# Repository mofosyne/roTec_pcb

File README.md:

# roTec_pcb

<details>
<summary>Revision 5.4 (Though Hole Version)</summary>

| Front (Through Hole Version)        | Back (Through Hole Version)       |
|:------------------------------------|:----------------------------------|
|  |  |

[Release Files For PCB Revision 5.4 (Though Hole Version)](https://github.com/mofosyne/roTec_pcb/releases/tag/rev5.4)

</details>

<details>
<summary>Revision 5.3 (Surface Mount)</summary>

| Front                               | Back                              |
|:------------------------------------|:----------------------------------|
|  |  |

[Release Files For PCB Revision 5.3 (All features except for GPS tested) (Recommended)](https://github.com/mofosyne/roTec_pcb/releases/tag/rev5.3)

</details>

RoTec is a low-cost nRF52 device with the form-factor of the Heltec v2, v3, & v4 devices compatible with [Meshtastic](https://meshtastic.org/)®, designed for use with rotary encoders as well as being easy to follow for less technical users.

The history of this design is that it is a fork of [Jacob's](https://github.com/jtljac) fork of the fakeTec.

This design is specifically based off of [Šimon Hořánek's](https://github.com/ShimonHoranek) [fakeTec V5 Rev. B](https://github.com/gargomoma/fakeTec_pcb/issues/24), licensed under [CERN-OHL-P-2.0](https://choosealicense.com/licenses/cern-ohl-p-2.0/).

**[For more meshtastic/meshcore/lora DIY nodes, do check this list out!](https://github.com/porkcube/meshtastic-diy-nodes)**

## Design Documentations (Through Hole Version)

* [Schematic as pdf](./Circuit_Through_Hole/documentation/roTec_schematic.pdf)
* [Schematic Bill Of Materials](./Circuit_Through_Hole/documentation/roTec_bom.csv)

* You may also want to manufacture [EC11 Rotary Encoder Horizontal Breakout Board](https://github.com/mofosyne/kicad_useful_pcbs/tree/main?tab=readme-ov-file#ec11-horizontal-breakout-board), so you can more easily wire the rotary encoder to the roTec via a JST-SH-4 cable.

This has the same parts list as the SMD version, but with a few parts subtracted.

## Design Documentations (Surface Mount Version)

* [Schematic as pdf](./Circuit/documentation/roTec_schematic.pdf)
* [Schematic Bill Of Materials](./Circuit/documentation/roTec_bom.csv)

* You may also want to manufacture [EC11 Rotary Encoder Horizontal Breakout Board](https://github.com/mofosyne/kicad_useful_pcbs/tree/main?tab=readme-ov-file#ec11-horizontal-breakout-board), so you can more easily wire the rotary encoder to the roTec via a JST-SH-4 cable.

### Bill of materials

<details>
<summary>Bill of material. For full details and descriptions refer to the csv BOM above instead.</summary>

| Reference           | Value                      | Qty | Manufacturer                     | MPN                  | Package                                | Datasheet                                                                                                                                     | Manufacturer Parts Link (MPL)                                                                                                                                                              | Shopping                                                                                                                                         |
|---------------------|----------------------------|-----|----------------------------------|----------------------|----------------------------------------|-----------------------------------------------------------------------------------------------------------------------------------------------|--------------------------------------------------------------------------------------------------------------------------------------------------------------------------------------------|--------------------------------------------------------------------------------------------------------------------------------------------------|
| J9                  | Molex PicoBlade 0532610271 | 1   | CJT(Changjiang Connectors)       | A1251WR-S-2P         | SMD,P=1.25mm,Surface Mount,Right Angle | [datasheet](https://www.molex.com/content/dam/molex/molex-dot-com/products/automated/en-us/salesdrawingpdf/532/53261/532610271_sd.pdf?inline) | [lcsc](https://www.lcsc.com/product-detail/C225111.html)                                                                                                                                   | [LCSC](https://www.lcsc.com/search?q=0532610271&s_z=n_0532610271)                                                                                |
| U1                  | XB8089D0 BMS               | 1   | XySemi                           | XB8089D0             | SOIC-8                                 | [datasheet](https://www.lcsc.com/datasheet/lcsc_datasheet_2410121637_XySemi-XB8089D0_C2760005.pdf                                           ) | [lcsc](https://www.lcsc.com/product-detail/C2760005.html?s_z=n_XySemi%2520XB8089D0)                                                                                                        | [LCSC](https://www.lcsc.com/search?q=XB8089D0&s_z=n_XB8089D0)                                                                                    |
| Q1,Q2,Q3            | n-chn mosfet               | 3   | Alpha & Omega Semiconductor Inc. | AO3400A              | SOT-23-3L                              | [datasheet](http://www.aosmd.com/pdfs/datasheet/AO3400A.pdf                                                                                 ) | [lcsc](https://www.lcsc.com/product-detail/C20917.html?s_z=n_AO3400A)                                                                                                                      | [LCSC](https://www.lcsc.com/search?q=MOSFET%2520N-CH%2520SOT-23-3L&s_z=n_MOSFET%2520N-CH%2520SOT-23-3L)                                          |
| BZ1                 | Buzzer 5020                | 1   | HYDZ                             | HYG-5020A            | SMD,5x5mm                              | [datasheet](https://www.lcsc.com/datasheet/C7544810.pdf                                                                                     ) | [lcsc](https://www.lcsc.com/product-detail/C7544810.html?s_z=n_buzzer%25205020)                                                                                                            | [LCSC](https://www.lcsc.com/search?q=Buzzer_5020&s_z=n_Buzzer_5020)                                                                              |
| J38,J50             | JST-SH-4                   | 2   | JST Sales America Inc.           | SM04B-SRSS-TB        | SMD,P=1mm,Surface Mount,Right Angle    | [datasheet](https://www.jst-mfg.com/product/pdf/eng/eSH.pdf                                                                                 ) | [lcsc](https://www.lcsc.com/product-detail/C51940130.html?s_z=n_SM04B-SRSS-TB)                                                                                                             | [LCSC](https://www.lcsc.com/search?q=SM04B-SRSS-TB&s_z=n_SM04B-SRSS-TB)                                                                          |
| OLED1               | I2C OLED Module            | 1   |                                  |                      | Through Hole                           | [datasheet](https://cdn-shop.adafruit.com/datasheets/SSD1306.pdf                                                                            ) | [aliexpress](https://www.aliexpress.com/item/1005008738379315.html)                                                                                                                        | [aliexpress](https://www.aliexpress.com/w/wholesale-0.96-Inch-OLED-Display-Module.html)                                                          |
| U3                  | nice!nano v2               | 1   | Nice!                            | nice!nano v2         | nice!nano v2                           | [datasheet](https://nicekeyboards.com/docs/nice-nano/pinout-schematic                                                                       ) | [aliexpress](https://www.aliexpress.com/item/1005010222966695.html)                                                                                                                        | [aliexpress](https://www.aliexpress.com/w/wholesale-NRF52840-1%2525252d10PCS.html)                                                               |
| SW1                 | Reset                      | 1   | XUNPU                            | TS-1088R-02026       | SMD,4x3mm                              | [datasheet](https://www.lcsc.com/datasheet/C455280.pdf                                                                                      ) | [lcsc](https://www.lcsc.com/product-detail/C455280.html?s_z=n_TS-1088R-02026)                                                                                                              | [LCSC](https://www.lcsc.com/search?q=TS-1088R-02026&s_z=n_TS-1088R-02026)                                                                        |
| SW2                 | SW_Push                    | 1   | XUNPU                            | TS-1088R-02026       | SMD,4x3mm                              | [datasheet](https://www.lcsc.com/datasheet/C455280.pdf                                                                                      ) | [lcsc](https://www.lcsc.com/product-detail/C455280.html?s_z=n_TS-1088R-02026)                                                                                                              | [LCSC](https://www.lcsc.com/search?q=TS-1088R-02026&s_z=n_TS-1088R-02026)                                                                        |
| R1,R2,R3,R9,R10,R11 | 10k                        | 6   |                                  |                      | 0805                                   |                                                                                                                                               |                                                                                                                                                                                            | [LCSC](https://www.lcsc.com/search?q=10K%25200805&s_z=n_10K%25200805)                                                                            |
| R4                  | 680K                       | 1   |                                  |                      | 0805                                   |                                                                                                                                               |                                                                                                                                                                                            | [LCSC](https://www.lcsc.com/search?q=680K%25200805&s_z=n_680K%25200805)                                                                          |
| R5                  | 1.0M                       | 1   |                                  |                      | 0805                                   |                                                                                                                                               |                                                                                                                                                                                            | [LCSC](https://www.lcsc.com/search?q=1M%25200805&s_z=n_1M%25200805)                                                                              |
| R6                  | 1k                         | 1   |                                  |                      | 0805                                   |                                                                                                                                               |                                                                                                                                                                                            | [LCSC](https://www.lcsc.com/search?q=1k%25200805&s_z=n_1k%25200805)                                                                              |
| SW3                 | RotaryEncoder_Switch       | 1   | Same Sky (Formerly CUI Devices)  | ACZ11BR1E-15KQA1-12C | EC11                                   | [datasheet](https://www.cuidevices.com/product/resource/acz11.pdf                                                                           ) | [aliexpress](https://www.aliexpress.com/item/1005010398201852.html) or [digikey](https://www.digikey.com.au/en/products/detail/same-sky-formerly-cui-devices/ACZ11BR1E-15KQA1-12C/1923334) | [aliexpress](https://www.aliexpress.com/w/wholesale-rotary-encoder-EC11-horizontal.html) or [digikey](https://www.digikey.com.au/short/7v5m7j9j) |
| U2                  | HT-RA62                    | 1   | Heltec                           | HT-RA62              | HT-RA62                                | [datasheet](https://resource.heltec.cn/download/HT-RA62/HT-RA62(Rev1.1).pdf                                                                 ) | [aliexpress](https://www.aliexpress.com/item/1005005543917617.html)                                                                                                                        | [aliexpress](https://www.aliexpress.com/w/wholesale-HT%2525252dRA62.html)                                                                        |
| C1,C2               | 100nF                      | 2   |                                  |                      | 0805                                   |                                                                                                                                               |                                                                                                                                                                                            | [LCSC](https://www.lcsc.com/search?q=100nF%25200805&s_z=n_100nF%25200805)                                                                        |
| M1                  | ERM Motor                  | 1   | Seeed Technology Co., Ltd        | 316040001            | Wire Leads                             | [datasheet](https://mm.digikey.com/Volume0/opasdata/d220001/medias/docus/2234/1020-15-003-001_Spec.pdf                                      ) | [digikey](https://www.digikey.com.au/en/products/detail/seeed-technology-co-ltd/316040001/5487672)                                                                                         | [aliexpress](https://www.digikey.com.au/short/332zpfdb)                                                                                          |

Purchase Tips:
* You can often buy SMD resistor kits in booklets from most places like amazon or aliexpress.
* Both nice!nano and promicro versions are supported
* You can swap the AO3400A n-channel mosfet with other higher current mosfet like SI2312 as long as the pins and packaqe size matches.
* Vibrations motors can be purchased in bulk pretty cheaply in aliexpress, ebay, amazon, etc...
* XB8089D0 BMS can be skipped if your battery have integrated battery protection already
* JST-SH-4 is optional if you want to solder the rotary encoder, gps, or i2c sensors directly onto the solder pads provided on the board instead
* For GPS support you can buy either ATGM336H or GY-GPS6MV2 modules
* Any OLED screen can be used. Pick one that is designed for your case. Often it's an SSD1306 controller based OLED screen.
* Any lora radios seen inside this [reference schematic](https://github.com/meshtastic/firmware/blob/develop/variants/nrf52840/diy/nrf52_promicro_diy_tcxo/Schematic_Pro-micro_Pinouts_2025-12-04.pdf) that fits the footprint and pinout is supported
  - Just like the faketecs you can also use RA-01SH.
* This design supports 3 different battery connectors types
  - Molex Picoblade 2-Pin
    - MPC: Molex, MPN: 0532610271
    - MPC: CJT (Changjiang Connectors), MPN: A1251WR-S-2P
    - Pitch: 1.25mm
    - Used By: HelTec LoRa 32
  - JST PH 2-Pin
    - MPN: S2B-PH-SM4-TB
    - Pitch: 2.00mm 
    - Used By: RAK19007 WisBlock
  - Direct wiring. 
    - e.g. JST-PH-2 but as an external wire like this [aliexpress product](https://www.aliexpress.com/item/1005002564191148.html)

</details>

## Setting Up Device

### Configure

Included in this repository is `roTec_module_config.yaml` which when you run below command will configure the buzzer, vibration motor and encoder.

```
PORT=/dev/ttyACM0 # Set to the serial port of the roTec after flashing
meshtastic --port $PORT --info
meshtastic --port $PORT --configure roTec_module_config.yaml
meshtastic --port $PORT --reboot
```

Alternatively you could manually use the web interface to set the settings using <client.meshtastic.org> as shown below
(No GPS settings it's already enabled by default if the module is installed).

#### Rotary Encoder Settings:

| Settings                                          | Value   |
|---------------------------------------------------|---------|
| module_config.cannedMessage.allowInputSource      | rotEnc1 |
| module_config.cannedMessage.enabled               | true    |
| module_config.cannedMessage.inputbrokerEventCcw   | RIGHT   |
| module_config.cannedMessage.inputbrokerEventCw    | LEFT    |
| module_config.cannedMessage.inputbrokerEventPress | SELECT  |
| module_config.cannedMessage.inputbrokerPinA       | 33      |
| module_config.cannedMessage.inputbrokerPinB       | 34      |
| module_config.cannedMessage.inputbrokerPinPress   | 39      |
| module_config.cannedMessage.rotary1Enabled        | true    |

#### Vibration Notification Settings:

| Settings                                             | Value |
|------------------------------------------------------|-------|
| module_config.externalNotification.enabled           | true  |
| module_config.externalNotification.alertBell         | true  |
| module_config.externalNotification.alertBellVibra    | true  |
| module_config.externalNotification.alertMessageVibra | true  |
| module_config.externalNotification.outputVibra       | 8     |

#### Buzzer Settings:

**Note you have to override buzzer gpio in config device page**

| Settings                                              | Value                                                                                                     |
|-------------------------------------------------------|-----------------------------------------------------------------------------------------------------------|
| config.device.buzzerGpio                              | 6                                                                                                         |
| module_config.externalNotification.enabled            | true                                                                                                      |
| module_config.externalNotification.alertBell          | true                                                                                                      |
| module_config.externalNotification.alertBellBuzzer    | true                                                                                                      |
| module_config.externalNotification.alertMessageBuzzer | true                                                                                                      |
| module_config.externalNotification.outputBuzzer       | 6                                                                                                         |
| module_config.externalNotification.usePwm             | true                                                                                                      |
| ringtone                                              | `24:d=32,o=5,b=565:f6,p,f6,4p,p,f6,p,f6,2p,p,b6,p,b6,p,b6,p,b6,p,b,p,b,p,b,p,b,p,b,p,b,p,b,p,b,1p.,2p.,p` |

## Features
- Small size based on Heltec v3: You can use the same cases!
- Lora with Heltec's HT-RA62
- Uses a [n!cenano](https://nicekeyboards.com/nice-nano/) or 
  [NRF52840 ProMicro](https://github.com/joric/nrfmicro/wiki/Alternatives#supermini-nrf52840l)
- BMS For low voltage cutout to prevent LiPo Overdraining
- Battery level sensing
- JST PH2.0mm connector for batteries
- I2C side ports ready to connect an OLED SSD1306 screen.
- Pads for connecting an encoder for canned messages
- Pads for connecting a serial GPS module
- MOSFETs for switching high current components
  - Using a solder pad jumper, MOSFET 1 can chose between the GPS module ground to enable power saving the GPS module, 
    or a regular pad like MOSFETs 2 & 3.
- 2mm mounting holes

## Modifications from fakeTec V5 Rev. B
- Cleaned up schematic
  - Changed Pins representing sides of MCUs to symbols fully representing said MCU
  - Changed labels to my preferred naming scheme
  - Updated/Cleaned up symbol fields to make each component easier to find
    - MPN: Manufacturer Parts Number
    - MPD: Manufacturer Parts Description
    - MPL: Manufacturer Parts Link
    - Shopping: Link to search pages used to locate parts. Useful for finding alternatives.
- Setup netclasses
- Shifted pads `P1.01`, `P1.02`, and `P1.07` to where I'm pretty sure they're supposed to be
- Removed jumper for BMS
  - I will always install a BMS
- Removed jumper for GPS/FET1 Drain to FET1
  - Only one will be connected at a time, probably no difference if this is permanently connected to both
- Switched mosfets to AO3400A
  - I already have these and they're a drop in replacement
- Changed all resistors and Capacitors to 805 sized
  - I already have all the resistors in this size
- Added pullup resistors to rotary encoder pads
  - These probably support internal pullups, but just to be safe
- Added ground pad to rotary encoder pads
- Changed battery connector to a JST PH-2.0mm
  - Struggled to find JST 1.25 connectors
  - PH-2.0mm are also apparently more reliable
- Removed lots of silkscreen text
  - Don't need values or component names, just component references
  - Most of it was overlapping
- Moved BMS to side
  - Keeps it out the way of the battery connector
- Added a lot more stitching between front and back ground planes
- Removed vias from on top of silkscreen and off of pads
- Attempted to reduce layer crossings
- Added test pads for the nice!nano/promicro to help users to figure out if the pads is correctly soldered down.
- Added connectors recommended by [this hackaday article ](https://hackaday.com/2022/05/04/the-connector-zoo-i2c-ecosystems) for easy attachment for i2c devices. Pads also exposed in case you want to solder the i2c device down.
- Added buzzer pads so that buzzer can be included in a more compact manner.
- Added pads to expose all the GPIO pins in case users want to use the GPIO for other purpose.
- Added additional marking to indicate resistance and capacitor values
- Added BMS bypass in case users are using batteries with integrated protection already

# Variants

(aka firmware files)

| Version      | Lora Modules                     | Official Repo link                                                                                                                                          | Unofficial Repo link                                                                                                                                                                |
|:-------------|:---------------------------------|:------------------------------------------------------------------------------------------------------------------------------------------------------------|:------------------------------------------------------------------------------------------------------------------------------------------------------------------------------------|
| With TCXO    | EByte E22/E220-xxxM-22S/HT-RA62  | <a href="https://github.com/meshtastic/firmware/tree/master/variants/nrf52840/diy/nrf52_promicro_diy_tcxo" target="_blank">Official repo - With TCXO</a>    | <a href="https://github.com/mrekin/MeshtasticCustomBoards/tree/main/firmware/variants/nrf52840/diy/promicro_diy_m" target="_blank">With TCXO</a> @mrekin/MeshtasticCustomBoards     |
| Without TCXO | EByte E22/E220-xxxMM-22S/RA-01SH | <a href="https://github.com/meshtastic/firmware/tree/master/variants/nrf52840/diy/nrf52_promicro_diy_xtal" target="_blank">Official repo - Without TCXO</a> | <a href="https://github.com/mrekin/MeshtasticCustomBoards/tree/main/firmware/variants/nrf52840/diy/promicro_diy_mm" target="_blank">Without TCXO</a> @mrekin/MeshtasticCustomBoards |

> If you don't want to build your own image use <a href="https://flasher.meshtastic.org/" target="_blank">the official web flasher</a>. Select the `NRF52 Pro-micro DIY` under `Community Supported Devices` as your target device.

# Supported Cases

Refer to [this page](./Cases/README.md) for details on supported cases that this design will fit into.

# About Meshtastic
[Meshtastic](https://meshtastic.org/)® is a registered trademark of Meshtastic LLC. Meshtastic software components are released under various licenses, see github for details.

# Disclaimer
No warranty is provided.
You use it at your own risk and take the responsibility upon yourself.

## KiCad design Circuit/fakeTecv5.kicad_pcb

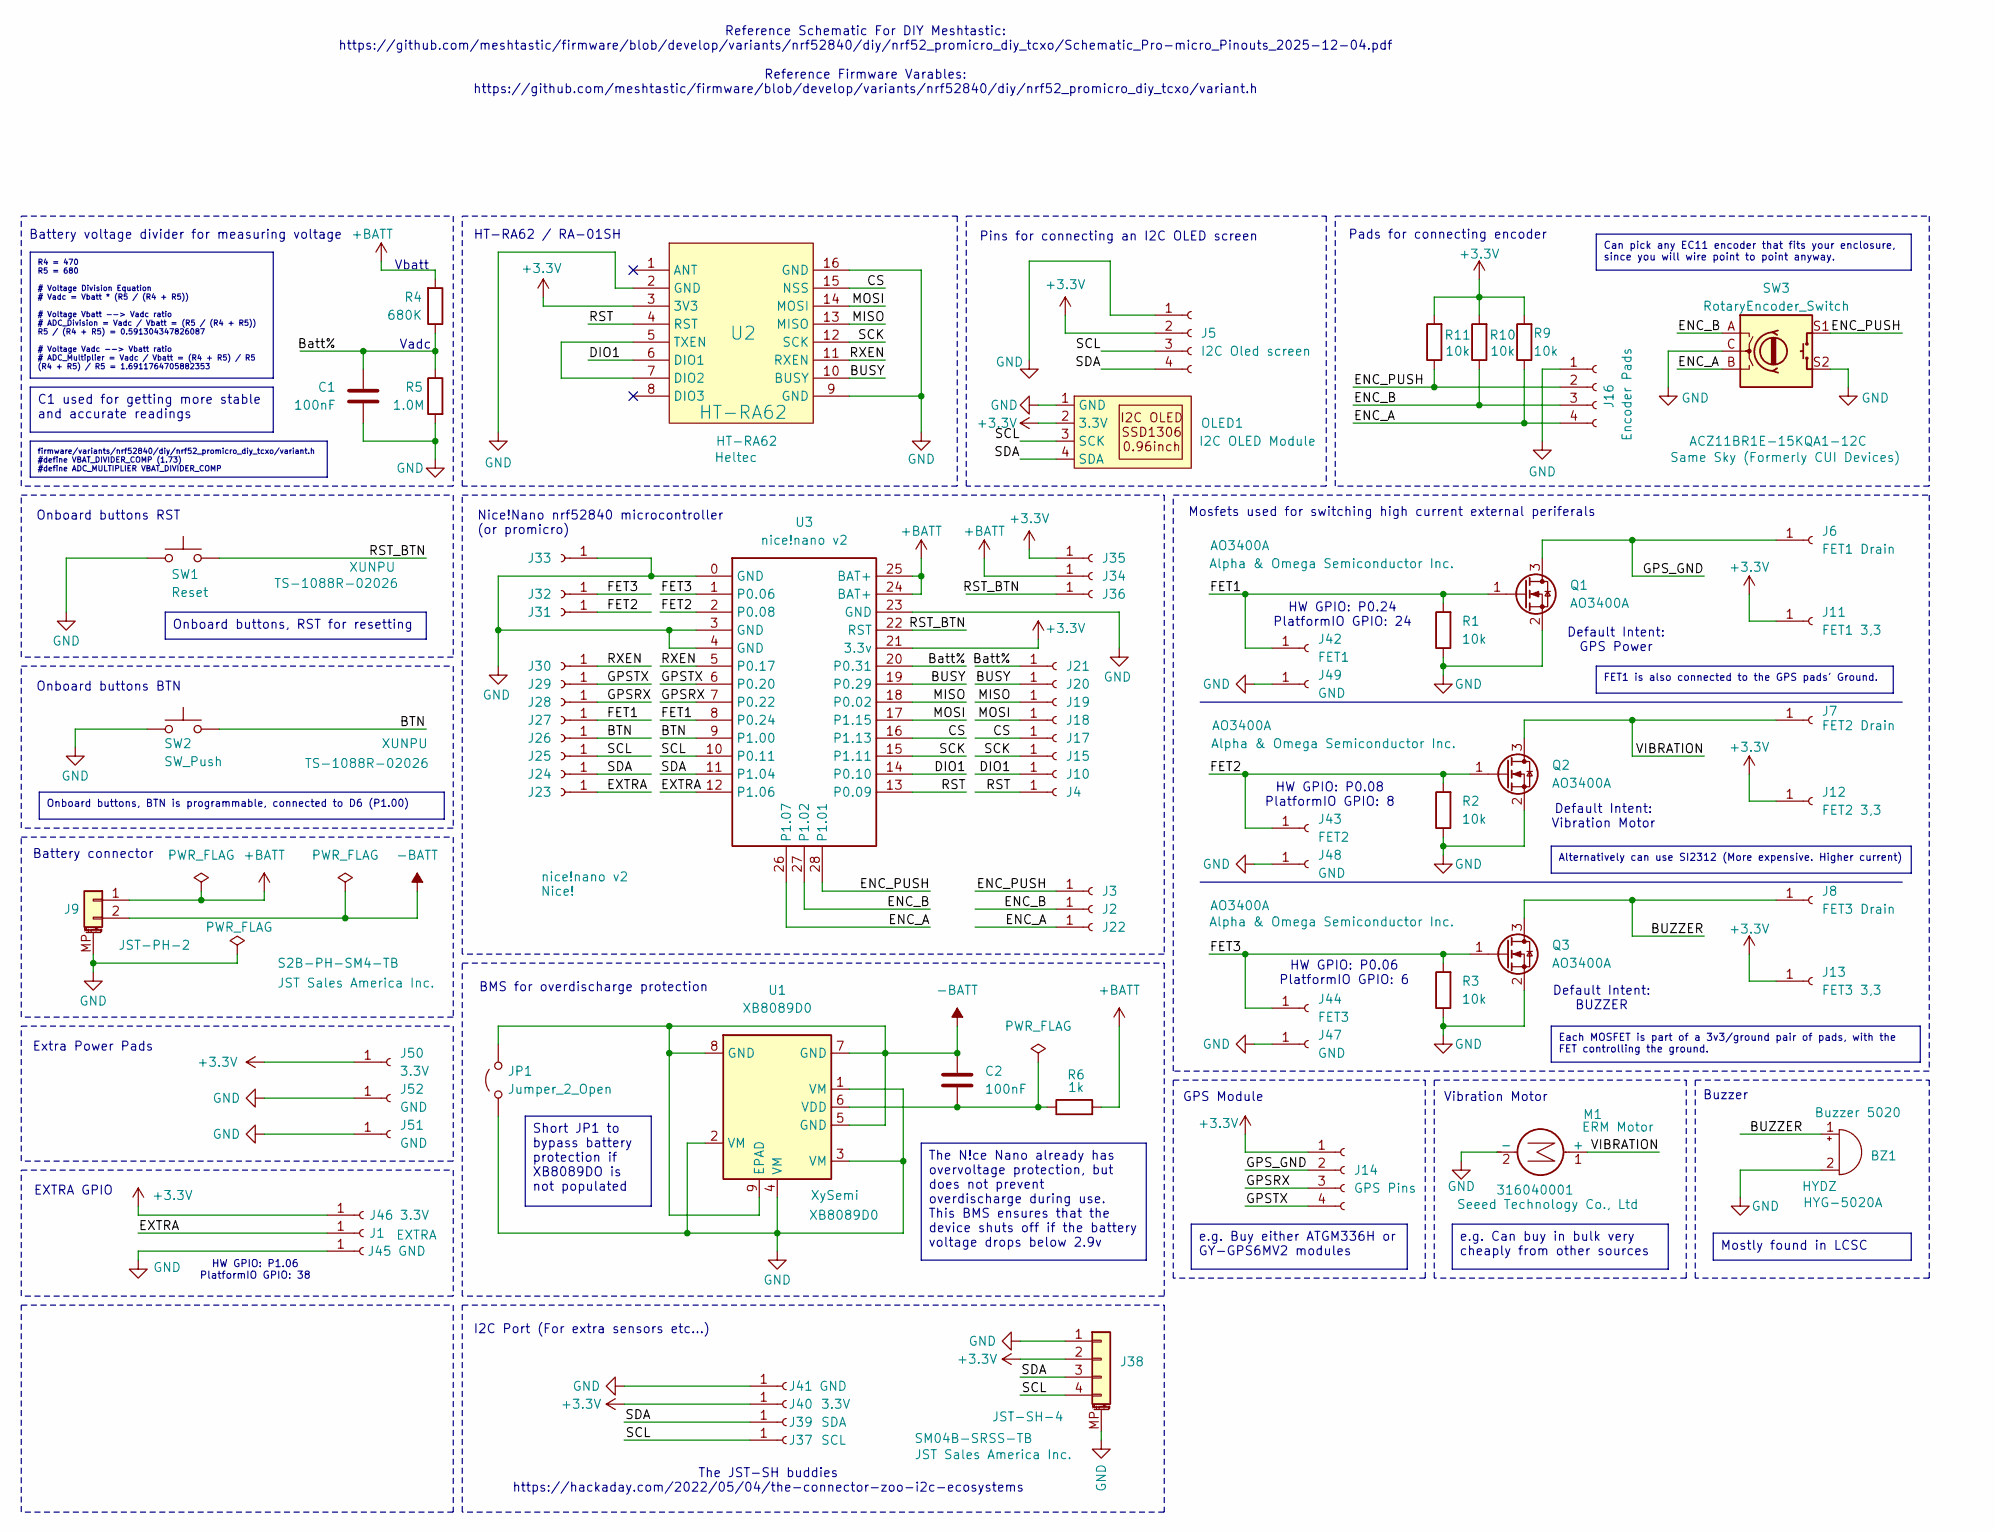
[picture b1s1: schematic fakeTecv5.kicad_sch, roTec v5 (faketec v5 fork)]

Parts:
BZ1: Buzzer 5020; Buzzer_5020; MPN HYG-5020A
C1, C2: 100nF; C_0805_2012Metric_Pad1.18x1.45mm_HandSolder
J1: EXTRA; SMD_PAD_1x01
J2, J3, J4, J10, J15, J17, J18, J19, J20, J21, J22, J23, J24, J25, J26, J27, J28, J29, J30, J31, J32, J33, J34, J35, J36: TestPoint_Pad_Slim_D0.6mm
J5: I2C Oled screen; PinHeader_1x04_P2.54mm_Vertical; MPN HX PZ2.54-1x4P ZZ
J6: FET1 Drain; SMD_PAD_1x01
J7: FET2 Drain; SMD_PAD_1x01
J8: FET3 Drain; SMD_PAD_1x01
J9: JST-PH-2; JST_PH_S2B-PH-SM4-TB_1x02-1MP_P2.00mm_Horizontal; MPN S2B-PH-SM4-TB
J11: FET1 3,3; SMD_PAD_1x01
J12: FET2 3,3; SMD_PAD_1x01
J13: FET3 3,3; SMD_PAD_1x01
J14: GPS Pins; SMD_PAD_1x04
J16: Encoder Pads; SMD_PAD_1x04
J37: SCL; SMD_PAD_1x01
J38: JST-SH-4; JST_SH_SM04B-SRSS-TB_1x04-1MP_P1.00mm_Horizontal; MPN SM04B-SRSS-TB
J39: SDA; SMD_PAD_1x01
J40, J46, J50: 3.3V; SMD_PAD_1x01
J41, J45, J47, J48, J49, J51, J52: GND; SMD_PAD_1x01
J42: FET1; SMD_PAD_1x01
J43: FET2; SMD_PAD_1x01
J44: FET3; SMD_PAD_1x01
JP1: Jumper_2_Open; SolderJumper-2_P1.3mm_Open_RoundedPad1.0x1.5mm
M1: ERM Motor; MPN 316040001
OLED1: I2C OLED Module
Q1, Q2, Q3: AO3400A; SOT-23_Handsoldering; MPN AO3400A
R1, R2, R3, R9, R10, R11: 10k; R_0805_2012Metric_Pad1.20x1.40mm_HandSolder
R4: 680K; R_0805_2012Metric_Pad1.20x1.40mm_HandSolder
R5: 1.0M; R_0805_2012Metric_Pad1.20x1.40mm_HandSolder
R6: 1k; R_0805_2012Metric_Pad1.20x1.40mm_HandSolder
SW1: Reset; SW_Push_SPST_NO_Alps_SKRK; MPN TS-1088R-02026
SW2: SW_Push; SW_Push_SPST_NO_Alps_SKRK; MPN TS-1088R-02026
SW3: RotaryEncoder_Switch; MPN ACZ11BR1E-15KQA1-12C
U1: XB8089D0; SOIC-8-1EP_3.9x4.9mm_P1.27mm_EP2.41x3.3mm; MPN XB8089D0
U2: HT-RA62; MPN HT-RA62
U3: nice!nano v2; NICE!NANO and pro-micro V2_2 SMD; MPN nice!nano v2

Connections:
+3.3V: J5.2, J11.1, J12.1, J13.1, J14.1, J35.1, J38.2, J40.1, J46.1, J50.1, OLED1.2 (3.3V), R9.2, R10.2, R11.2, U2.3 (3V3), U3.21 (3.3v)
+BATT: J9.1, J34.1, R4.2, R6.2, U3.24 (BAT+), U3.25 (BAT+)
-BATT: C2.1, J9.2, JP1.2 (B), U1.5 (GND), U1.7 (GND), U1.8 (GND), U1.9 (EPAD)
/BTN: J26.1, SW2.2, U3.9 (P1.00)
/BUSY: J20.1, U2.10 (BUSY), U3.19 (P0.29)
/BUZZER: BZ1.1 (+), J8.1, Q3.3 (D)
/Batt%: C1.1, J21.1, R4.1, R5.1, U3.20 (P0.31)
/CS: J17.1, U2.15 (NSS), U3.16 (P1.13)
/DIO1: J10.1, U2.6 (DIO1), U3.14 (P0.10)
/ENC_A: J16.4, J22.1, R9.1, SW3.B, U3.26 (P1.07)
/ENC_B: J2.1, J16.3, R10.1, SW3.A, U3.27 (P1.02)
/ENC_PUSH: J3.1, J16.2, R11.1, SW3.S1, U3.28 (P1.01)
/EXTRA: J1.1, J23.1, U3.12 (P1.06)
/FET1: J27.1, J42.1, Q1.1 (G), R1.2, U3.8 (P0.24)
/FET2: J31.1, J43.1, Q2.1 (G), R2.2, U3.2 (P0.08)
/FET3: J32.1, J44.1, Q3.1 (G), R3.2, U3.1 (P0.06)
/GPSRX: J14.3, J28.1, U3.7 (P0.22)
/GPSTX: J14.4, J29.1, U3.6 (P0.20)
/GPS_GND: J6.1, J14.2, Q1.3 (D)
/MISO: J19.1, U2.13 (MISO), U3.18 (P0.02)
/MOSI: J18.1, U2.14 (MOSI), U3.17 (P1.15)
/RST: J4.1, U2.4 (RST), U3.13 (P0.09)
/RST_BTN: J36.1, SW1.2, U3.22 (RST)
/RXEN: J30.1, U2.11 (RXEN), U3.5 (P0.17)
/SCK: J15.1, U2.12 (SCK), U3.15 (P1.11)
/SCL: J5.3, J25.1, J37.1, J38.4, OLED1.3 (SCK), U3.10 (P0.11)
/SDA: J5.4, J24.1, J38.3, J39.1, OLED1.4 (SDA), U3.11 (P1.04)
GND: BZ1.2 (-), C1.2, J5.1, J9.MP (MountPin), J16.1, J33.1, J38.1, J38.MP (MountPin), J41.1, J45.1, J47.1, J48.1, J49.1, J51.1, J52.1, JP1.1 (A), M1.2 (-), OLED1.1 (GND), Q1.2 (S), Q2.2 (S), Q3.2 (S), R1.1, R2.1, R3.1, R5.2, SW1.1, SW2.1, SW3.C, SW3.S2, U1.1 (VM), U1.2 (VM), U1.3 (VM), U1.4 (VM), U2.2 (GND), U2.9 (GND), U2.16 (GND), U3.0 (GND), U3.3 (GND), U3.4 (GND), U3.23 (GND)
unnamed: J7.1, M1.1 (+), Q2.3 (D)
unnamed: C2.2, R6.1, U1.6 (VDD)
unnamed: U2.5 (TXEN), U2.7 (DIO2)

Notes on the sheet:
GPS Module
I2C Port (For extra sensors etc...)
Nice!Nano nrf52840 microcontroller (or promicro)
Pads for connecting encoder
Default Intent: GPS Power
Mosfets used for switching high current external periferals
BMS for overdischarge protection
The JST-SH buddies https://hackaday.com/2022/05/04/the-connector-zoo-i2c-ecosystems
Extra Power Pads
Battery voltage divider for measuring voltage
Reference Schematic For DIY Meshtastic: https://github.com/meshtastic/firmware/blob/develop/variants/nrf52840/diy/nrf52_promicro_diy_tcxo/Schematic_Pro-micro_Pinouts_2025-12-04.pdf Reference Firmware Varables: https://github.com/meshtastic/firmware/blob/develop/variants/nrf52840/diy/nrf52_promicro_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
Vibration Motor
HW GPIO: P0.24 PlatformIO GPIO: 24
HW GPIO: P0.06 PlatformIO GPIO: 6
HT-RA62 / RA-01SH
HW GPIO: P1.06 PlatformIO GPIO: 38
Onboard buttons RST
EXTRA GPIO
Battery connector
HW GPIO: P0.08 PlatformIO GPIO: 8
Buzzer
Default Intent: Vibration Motor
Vadc
Vbatt
Onboard buttons BTN
Pins for connecting an I2C OLED screen
Default Intent: BUZZER
FET1 is also connected to the GPS pads' Ground.
Alternatively can use SI2312 (More expensive. Higher current)
Mostly found in LCSC
Onboard buttons, BTN is programmable, connected to D6 (P1.00)
e.g. Buy either ATGM336H or GY-GPS6MV2 modules
Can pick any EC11 encoder that fits your enclosure, since you will wire point to point anyway.
Onboard buttons, RST for resetting
C1 used for getting more stable and accurate readings
e.g. Can buy in bulk very cheaply from other sources
R4 = 470 R5 = 680 # Voltage Division Equation # Vadc = Vbatt * (R5 / (R4 + R5)) # Voltage Vbatt --> Vadc ratio # ADC_Division = Vadc / Vbatt = (R5 / (R4 + R5)) R5 / (R4 + R5) = 0.591304347826087 # Voltage Vadc --> Vbatt ratio # ADC_Multiplier = Vadc / Vbatt = (R4 + R5) / R5 (R4 + R5) / R5 = 1.69117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
Each MOSFET is part of a 3v3/ground pair of pads, with the FET controlling the ground.
The N!ce Nano already has overvoltage protection, but does not prevent overdischarge during use. This BMS ensures that the device shuts off if the battery voltage drops below 2.9v
firmware/variants/nrf52840/diy/nrf52_promicro_diy_tcxo/variant.h #define VBAT_DIVIDER_COMP (1.73) #define ADC_MULTIPLIER VBAT_DIVIDER_COMP

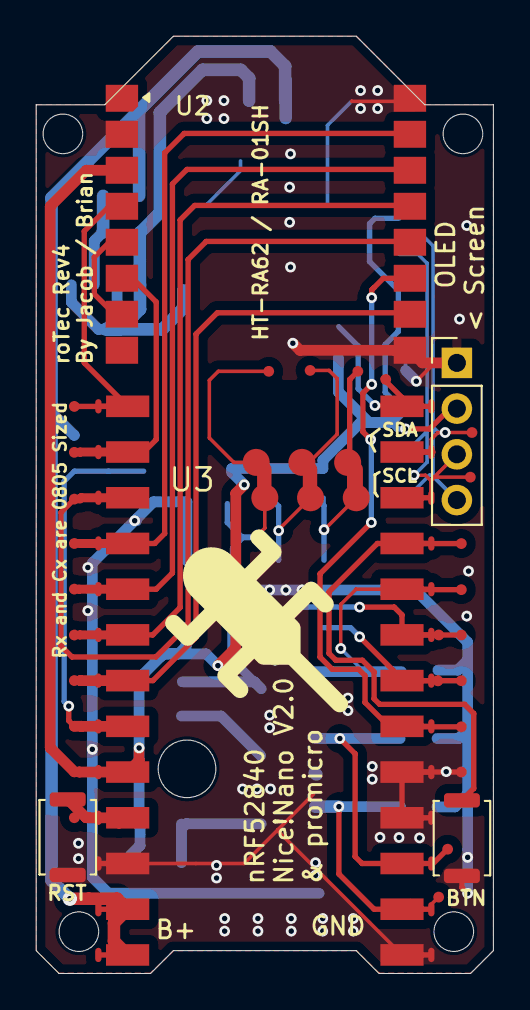
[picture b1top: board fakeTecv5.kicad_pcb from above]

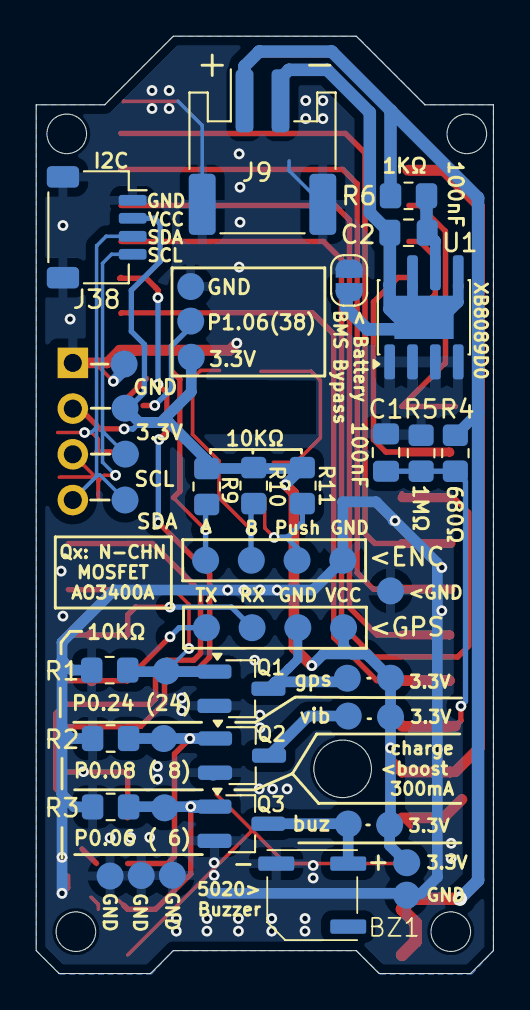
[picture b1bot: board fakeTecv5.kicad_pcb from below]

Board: 2 copper layers, 25.4 x 52.1 mm, 73 parts (43 on the bottom side), 31 nets.

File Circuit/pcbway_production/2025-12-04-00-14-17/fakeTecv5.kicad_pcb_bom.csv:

Designator,Quantity,Value,Footprint,Package,MPN,DNP,Mount_Type,Description,ALTIUM_VALUE,Manufacturer
", , ",3,,,,,,tht,,,
BZ1,1,Buzzer,Buzzer_5020,,,,smt,"Buzzer, polarized",,
"C1, C2, C3, C4",4,100nF,C_0805_2012Metric_Pad1.18x1.45mm_HandSolder,,,,smt,Unpolarized capacitor,,
J11,1,"FET1 3,3",SMD_PAD_1x01,,,,smt,"Generic connector, single row, 01x01, script generated",,
J12,1,"FET2 3,3",SMD_PAD_1x01,,,,smt,"Generic connector, single row, 01x01, script generated",,
J13,1,"FET3 3,3",SMD_PAD_1x01,,,,smt,"Generic connector, single row, 01x01, script generated",,
J14,1,GPS Pins,SMD_PAD_1x04,,,,smt,"Generic connector, single row, 01x04, script generated",,
J16,1,Encoder Pads,SMD_PAD_1x04,,,,smt,"Generic connector, single row, 01x04, script generated",,
J23,1,~,TestPoint_Pad_Slim_D0.6mm,,,,tht,"Generic connector, single row, 01x01, script generated",,
J37,1,SCL,SMD_PAD_1x01,,,,smt,"Generic connector, single row, 01x01, script generated",,
J38,1,QWIIC,JST_SH_SM04B-SRSS-TB_1x04-1MP_P1.00mm_Horizontal,,,,smt,"Generic connectable mounting pin connector, single row, 01x04, script generated (kicad-library-utils/schlib/autogen/connector/)",,
J39,1,SDA,SMD_PAD_1x01,,,,smt,"Generic connector, single row, 01x01, script generated",,
"J40, J46",2,3.3V,SMD_PAD_1x01,,,,smt,"Generic connector, single row, 01x01, script generated",,
"J41, J47, J48, J49",4,GND,SMD_PAD_1x01,,,,smt,"Generic connector, single row, 01x01, script generated",,
J42,1,FET1,SMD_PAD_1x01,,,,smt,"Generic connector, single row, 01x01, script generated",,
J43,1,FET2,SMD_PAD_1x01,,,,smt,"Generic connector, single row, 01x01, script generated",,
J44,1,FET3,SMD_PAD_1x01,,,,smt,"Generic connector, single row, 01x01, script generated",,
J5,1,I2C Oled screen,PinHeader_1x04_P2.54mm_Vertical,,,,tht,"Generic connector, single row, 01x04, script generated",,
J6,1,FET1 Drain,SMD_PAD_1x01,,,,smt,"Generic connector, single row, 01x01, script generated",,
J7,1,FET2 Drain,SMD_PAD_1x01,,,,smt,"Generic connector, single row, 01x01, script generated",,
J8,1,FET3 Drain,SMD_PAD_1x01,,,,smt,"Generic connector, single row, 01x01, script generated",,
J9,1,Battery Connector,JST_PH_S2B-PH-SM4-TB_1x02-1MP_P2.00mm_Horizontal,,,,smt,"Generic connectable mounting pin connector, single row, 01x02, script generated (kicad-library-utils/schlib/autogen/connector/)",,
JP1,1,Jumper_2_Open,SolderJumper-2_P1.3mm_Open_RoundedPad1.0x1.5mm,,,,tht,"Jumper, 2-pole, open",,
"Q1, Q2, Q3",3,AO3400A,SOT-23_Handsoldering,,,,smt,"30V Vds, 5.7A Id, N-Channel MOSFET, SOT-23",,
"R1, R10, R11, R2, R3, R7, R8, R9",8,10k,R_0805_2012Metric_Pad1.20x1.40mm_HandSolder,,,,smt,Resistor,,
R4,1,680K,R_0805_2012Metric_Pad1.20x1.40mm_HandSolder,,,,smt,Resistor,,
R5,1,1M,R_0805_2012Metric_Pad1.20x1.40mm_HandSolder,,,,smt,Resistor,,
R6,1,1k,R_0805_2012Metric_Pad1.20x1.40mm_HandSolder,,,,smt,Resistor,,
SW1,1,Reset,SW_Push_SPST_NO_Alps_SKRK,,,,smt,"Push button switch, generic, two pins",,
SW2,1,SW_Push,SW_Push_SPST_NO_Alps_SKRK,,,,smt,"Push button switch, generic, two pins",,
U1,1,XB8089D0,SOIC-8-1EP_3.9x4.9mm_P1.27mm_EP2.41x3.3mm,,,,smt,2.9V~6V Lithium-ion/Polymer 1 SOP-8-EP Battery Management ROHS,,
U2,1,HT-RA62,HT-RA62,,,,tht,The Heltec LoRa Series Module HT-RA62 was designed and developed by Heltec Automation.,HT-RA62,
U3,1,nice!nano v2,NICE!NANO and pro-micro V2_2 SMD,,,,smt,,,nice!

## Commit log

2025-11-11 Added pull up resistors and ground pad to rotary encoder pads
2025-12-03 renamed to rotTec and pcb artwork updated
2025-12-04 schematic layout update
2025-12-07 Rename from rotTec_pcb to roTec and pdf and clean up schematic and pcb
    Also add 3D printed case with fixed usb Type-C port position
2025-12-07 update bom
2025-12-07 bom shopping link typo
2025-12-07 clean up schematic and resolve all schematic design rule checks
2025-12-09 Removed resistor and capacitor for button and also add integrated test pads.
    Also added jlcpcb design rules
2025-12-09 adc multiplier notes adjusted
2025-12-10 improve documentation of battery voltage divider ratio
2025-12-11 bom update and added extra power pads for easier adjustments
2025-12-12 updated bom list and schematic with notes on finding all the parts
2025-12-12 background color in schematic
2025-12-12 rotate small i2c connector
2025-12-13 adjust i2c markings
2025-12-13 fix schematic typo
2025-12-13 update preview image
2026-01-10 sch: add more dev notes to explain why DIO1 and DIO2 is connected the way they were

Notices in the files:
README.md:
[Meshtastic](https://meshtastic.org/)® is a registered trademark of Meshtastic LLC. Meshtastic software components are released under various licenses, see github for details.
